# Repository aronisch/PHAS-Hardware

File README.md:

# PHAS-Hardware
Hardware Files of PHAS - Personal Home Automation System

- Base System : Raspberry Pi Zero W with my own Xbee3 RF PCB shield
- Accessories : For now, there is only a Switch for my HiFi Tube Amplifier (Power up or shutdown through HomeKit or the original Switch)
- Schematics and PCB made with Eagle
- TODO : A wood case for the Base System

## Software
See [PHAS](https://github.com/aronisch/PHAS)

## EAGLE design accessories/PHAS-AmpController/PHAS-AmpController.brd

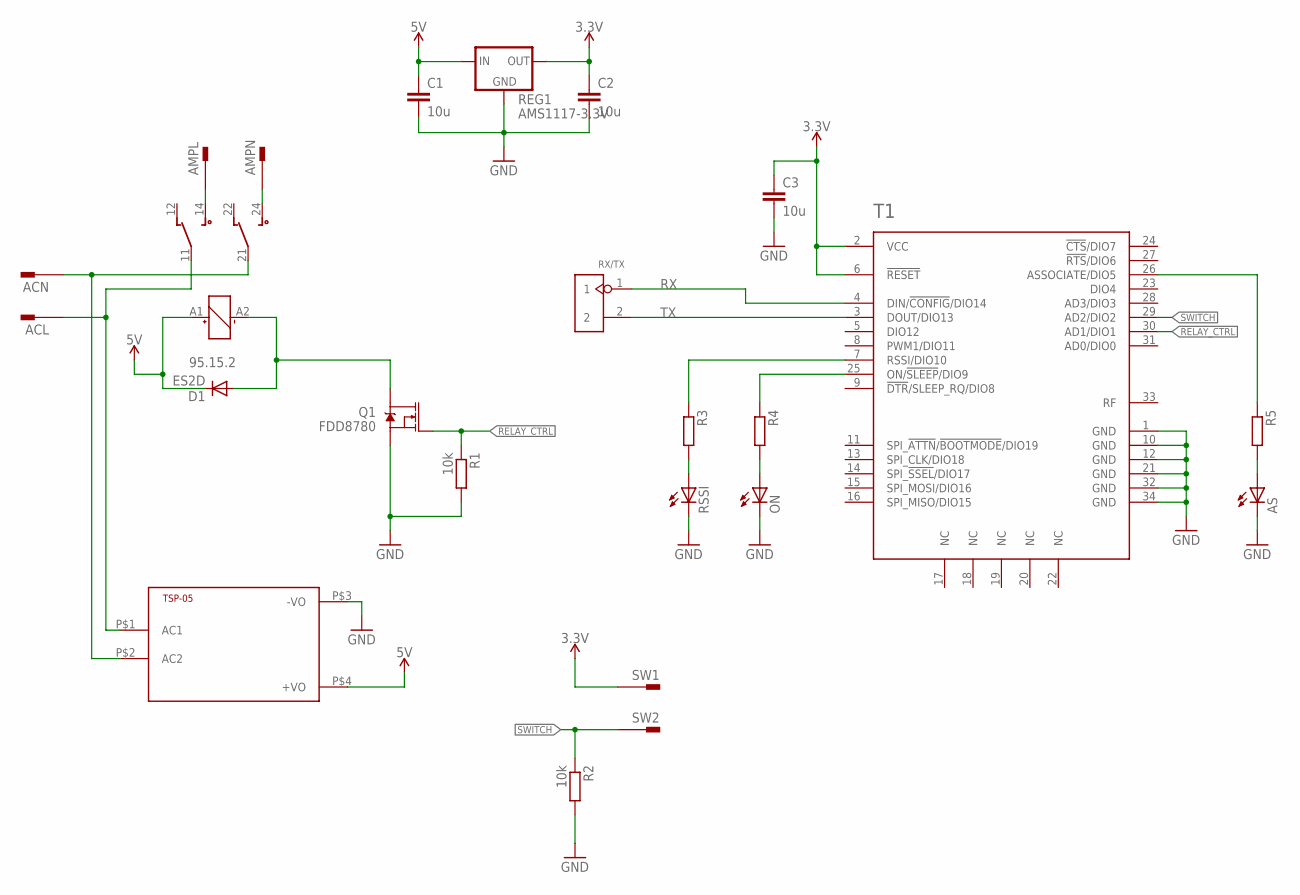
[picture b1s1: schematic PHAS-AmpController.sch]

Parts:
ACL: PIN2F061.100; F061.100
ACN: PIN2F061.100; F061.100
AMPL: PIN2F061.100; F061.100
AMPN: PIN2F061.100; F061.100
AS: LEDCHIPLED_0805; CHIPLED_0805
C1, C2, C3: 10u; C0805
D1: ES2D; SMB
ON: LEDCHIPLED_0805; CHIPLED_0805
Q1: FDD8780; DPAK
R1, R2: 10k; R0805
R3, R4, R5: R-EU_R0805; R0805
REG1: AMS1117-3.3V; SOT223
RL1: 95.15.2
RSSI: LEDCHIPLED_0805; CHIPLED_0805
RX/TX: DIP-BLACK-MALE-HEADER-VERT(2P-2.54); H2-2.54
SW1, SW2: PIN2F061.100; F061.100
T1: XBEE3-MICRO
TSP-05: HKLPM01

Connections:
3.3V: C2.1, C3.1, REG1.2 (OUT), REG1.4 (OUT), SW1.A1, SW1.A2, T1.2 (VCC), T1.6 (!RESET!)
5V: C1.1, D1.C, REG1.3 (IN), RL1.A1, TSP-05.P$4 (+VO)
GND: AS.C, C1.2, C2.2, C3.2, ON.C, Q1.3 (S), R1.2, R2.2, REG1.1 (GND), RSSI.C, T1.1 (GND), T1.10 (GND), T1.12 (GND), T1.21 (GND), T1.32 (GND), T1.34 (GND), TSP-05.P$3 (-VO)
unnamed: ACL.A1, ACL.A2, RL1.11, TSP-05.P$1 (AC1)
unnamed: R3.2, RSSI.A
unnamed: ON.A, R4.2
unnamed: D1.A, Q1.4 (D), RL1.A2
unnamed: AS.A, R5.2
unnamed: R3.1, T1.7 (RSSI/DIO10)
unnamed: R4.1, T1.25 (ON/!SLEEP!/DIO9)
unnamed: R5.1, T1.26 (ASSOCIATE/DIO5)
unnamed: AMPL.A1, AMPL.A2, RL1.14
unnamed: AMPN.A1, AMPN.A2, RL1.24
unnamed: ACN.A1, ACN.A2, RL1.21, TSP-05.P$2 (AC2)
RELAY_CTRL: Q1.1 (G), R1.1, T1.30 (AD1/DIO1)
RX: RX/TX.1, T1.4 (DIN/!CONFIG!/DIO14)
SWITCH: R2.1, SW2.A1, SW2.A2, T1.29 (AD2/DIO2)
TX: RX/TX.2, T1.3 (DOUT/DIO13)

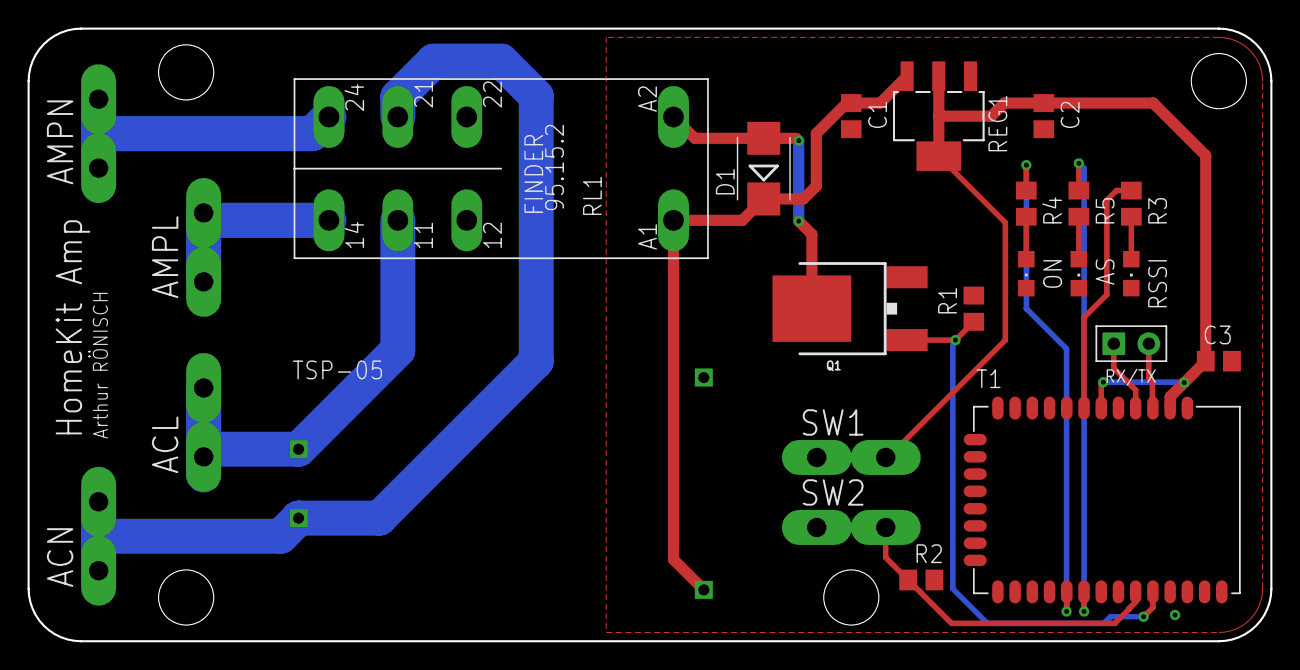
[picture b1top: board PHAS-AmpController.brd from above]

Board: 2 copper layers, 90.2 x 44.5 mm, 24 parts (0 on the bottom side), 18 nets.

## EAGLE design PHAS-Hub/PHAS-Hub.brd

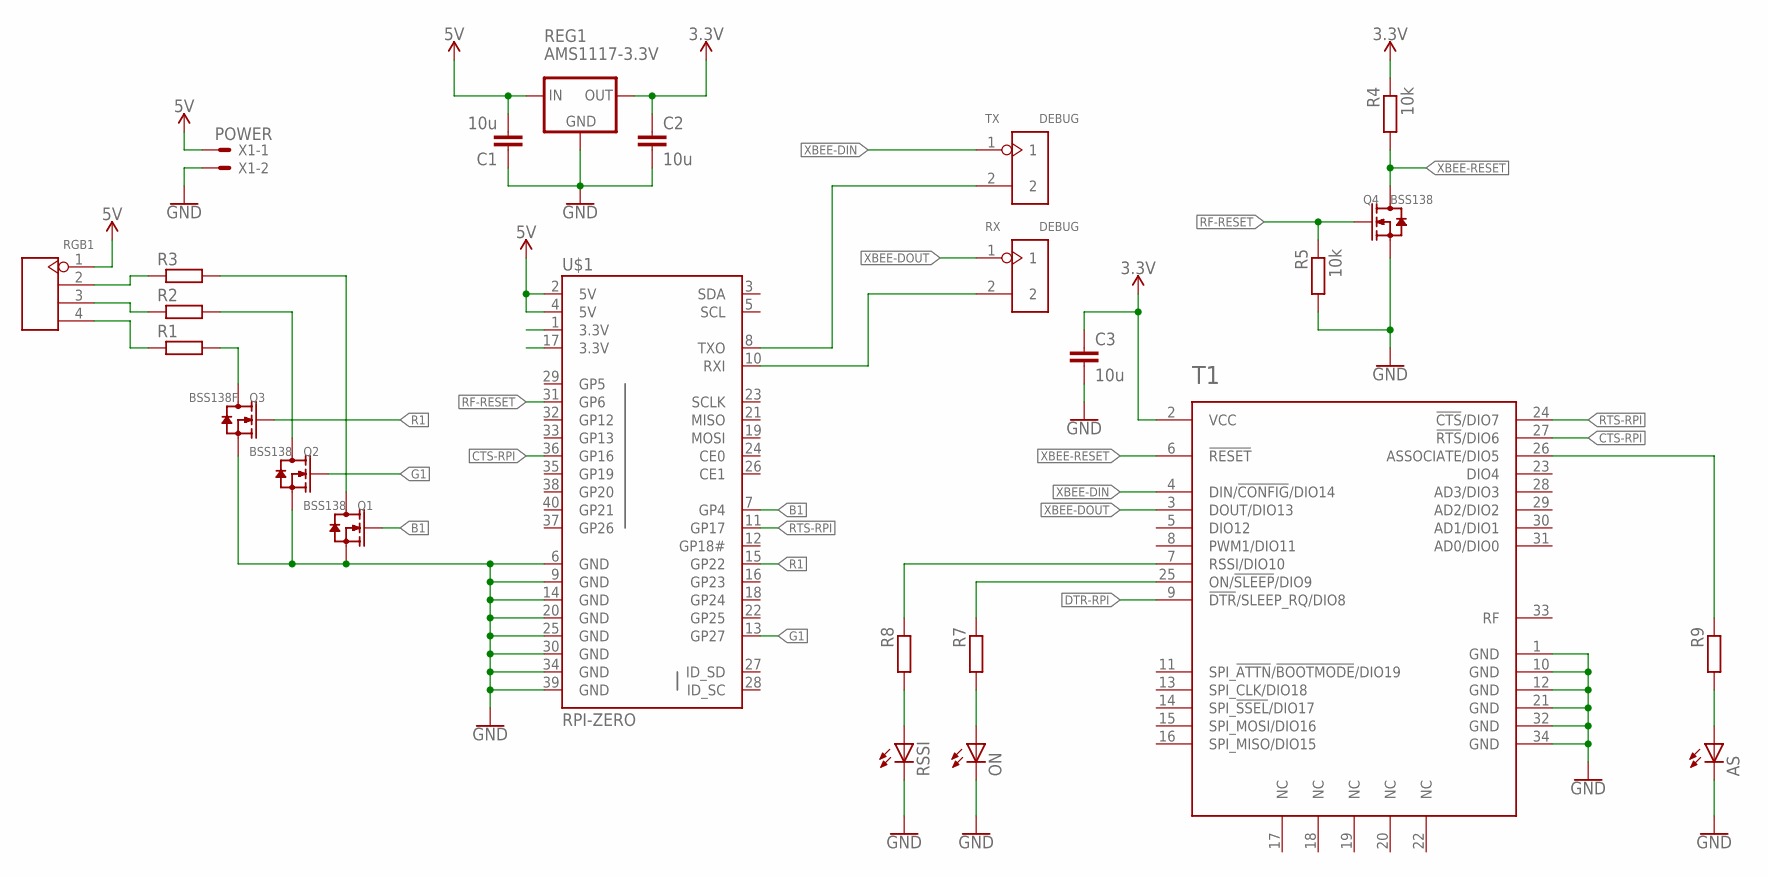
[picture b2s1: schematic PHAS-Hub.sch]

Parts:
AS: LEDCHIPLED_0805; CHIPLED_0805
C1, C2, C3: 10u; C0805
ON: LEDCHIPLED_0805; CHIPLED_0805
Q1, Q2, Q4: BSS138; SOT-23
Q3: BSS138F; SOT-23
R1, R2, R3, R7, R8, R9: R-EU_R0805; R0805
R4, R5: 10k; R0805
REG1: AMS1117-3.3V; SOT223
RGB1: DIP-BLACK-MALE-HEADER-VERT(4P-2.54); H4-2.54
RSSI: LEDCHIPLED_0805; CHIPLED_0805
RX: DEBUG; H2-2.54
T1: XBEE3-MICRO
TX: DEBUG; H2-2.54
U$1: RPI-ZERO; RASPBERRYPI_BASTELSTUBE_V13_RASPI_BOARD_B+_FULL
X1: POWER; 70543-02

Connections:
3.3V: C2.1, C3.1, R4.1, REG1.2 (OUT), REG1.4 (OUT), T1.2 (VCC)
5V: C1.2, REG1.3 (IN), RGB1.1, U$1.2 (5V), U$1.4 (5V), X1.1
B1: Q1.1 (G), U$1.7 (GP4)
CTS-RPI: T1.27 (!RTS!/DIO6), U$1.36 (GP16)
DTR-RPI: T1.9 (!DTR!/SLEEP_RQ/DIO8)
G1: Q2.1 (G), U$1.13 (GP27)
GND: AS.C, C1.1, C2.2, C3.2, ON.C, Q1.2 (S), Q2.2 (S), Q3.2 (S), Q4.2 (S), R5.2, REG1.1 (GND), RSSI.C, T1.1 (GND), T1.10 (GND), T1.12 (GND), T1.21 (GND), T1.32 (GND), T1.34 (GND), U$1.6 (GND), U$1.9 (GND), U$1.14 (GND), U$1.20 (GND), U$1.25 (GND), U$1.30 (GND), U$1.34 (GND), U$1.39 (GND), X1.2
unnamed: TX.2, U$1.8 (TXO)
unnamed: RX.2, U$1.10 (RXI)
unnamed: Q3.3 (D), R1.2
unnamed: Q2.3 (D), R2.2
unnamed: Q1.3 (D), R3.2
unnamed: AS.A, R9.2
unnamed: R7.1, T1.25 (ON/!SLEEP!/DIO9)
unnamed: R8.2, RSSI.A
unnamed: R3.1, RGB1.2
unnamed: R2.1, RGB1.3
unnamed: R1.1, RGB1.4
unnamed: ON.A, R7.2
unnamed: R8.1, T1.7 (RSSI/DIO10)
unnamed: R9.1, T1.26 (ASSOCIATE/DIO5)
R1: Q3.1 (G), U$1.15 (GP22)
RF-RESET: Q4.1 (G), R5.1, U$1.31 (GP6)
RTS-RPI: T1.24 (!CTS!/DIO7), U$1.11 (GP17)
XBEE-DIN: T1.4 (DIN/!CONFIG!/DIO14), TX.1
XBEE-DOUT: RX.1, T1.3 (DOUT/DIO13)
XBEE-RESET: Q4.3 (D), R4.2, T1.6 (!RESET!)

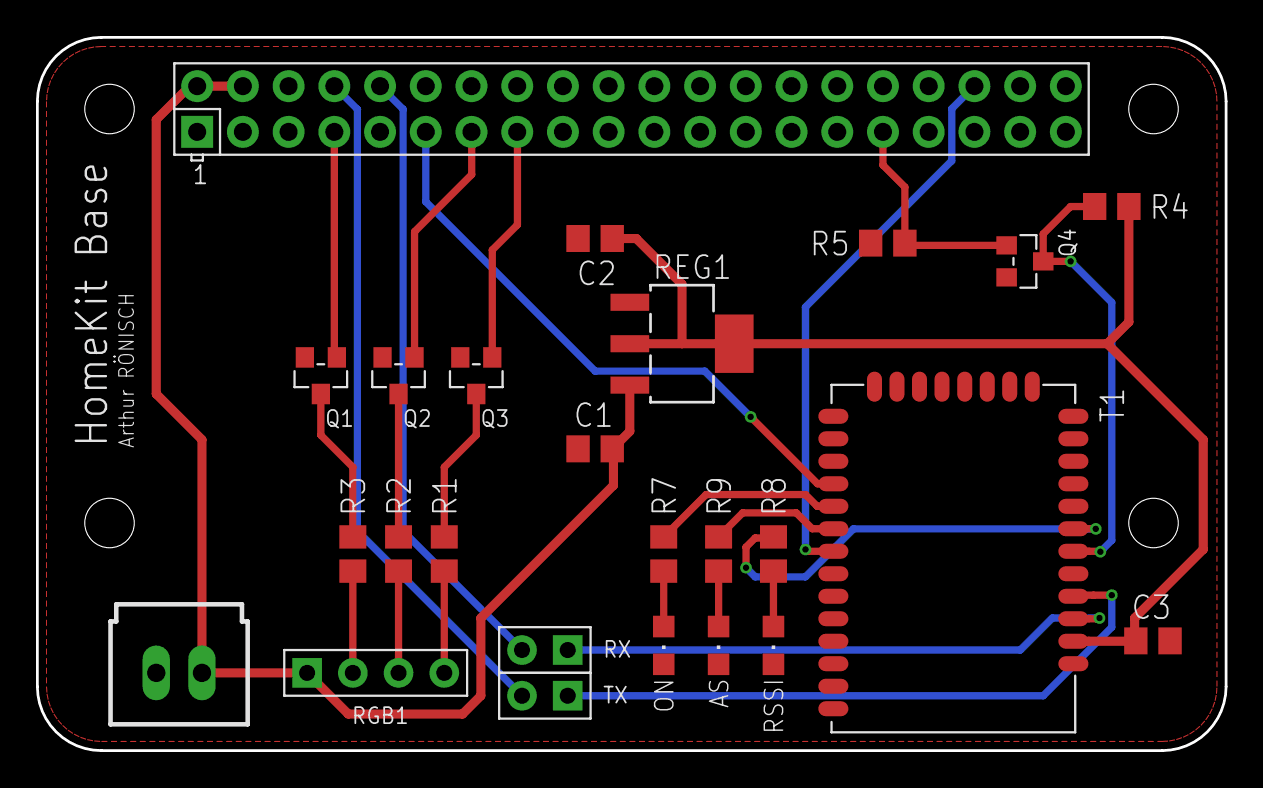
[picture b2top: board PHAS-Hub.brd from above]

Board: 2 copper layers, 66.0 x 39.6 mm, 25 parts (0 on the bottom side), 26 nets.

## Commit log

2018-07-14 Add initial boards

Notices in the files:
parts and their libraries:
SparkFun-PowerSymbols: Licensing: Creative Commons ShareAlike 4.0 International - https://creativecommons.org/licenses/by-sa/4.0
